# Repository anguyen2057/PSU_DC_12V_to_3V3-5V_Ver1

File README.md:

# PSU_DC_12V_to_3V3-5V_Ver1
Initial design compact switching power supply unit (PSU) that converts a 12V input to regulated 3.3V and 5V outputs.

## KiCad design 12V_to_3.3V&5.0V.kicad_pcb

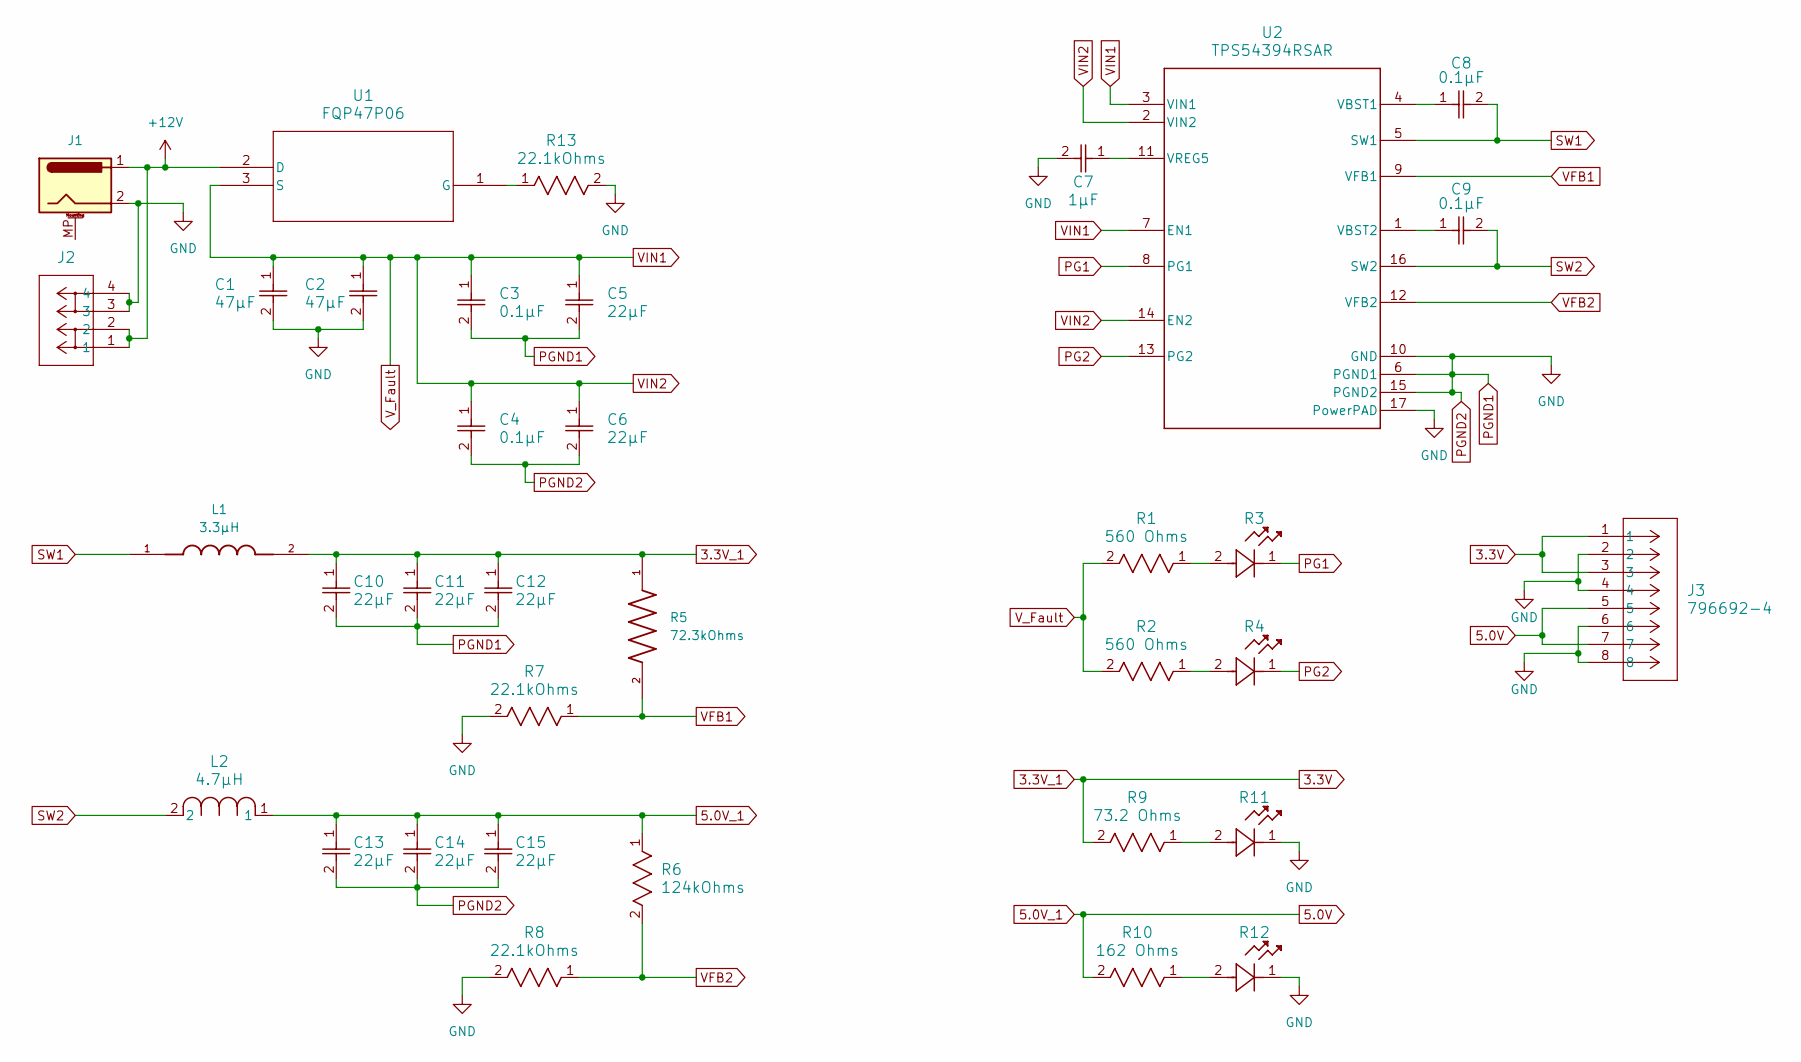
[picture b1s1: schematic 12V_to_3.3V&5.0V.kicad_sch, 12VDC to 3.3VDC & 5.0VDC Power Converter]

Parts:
C1, C2: 47µF; CAP_3216_TDK-M
C3, C4, C8, C9: 0.1µF; CAP_1005_TDK-M
C5, C6, C10, C11, C12, C13, C14, C15: 22µF; CAP_3216_TDK-M
C7: 1µF; CAP_2012_TDK-M
J1: Barrel_Jack_MountingPin; BarrelJack_Wuerth_6941xx301002
J2: 1017503; CONN_1017491
J3: 796692-4; CONN8_796692-4_TEC
L1: 3.3µH; IND_VLS6045EX-3R3N; PARTREV N/A; DigiKey_Part_Number 445-173052-2-ND
L2: 4.7µH; IND_VLS6045EX-4R7M_TDK-M
R1, R2: 560 Ohms; RC1206N_YAG-M
R3, R4, R11, R12: SML-E12DWT86; LED_SMLD12_ROM
R5: 72.3kOhms; RESC1608X55N; DigiKey_Part_Number 2019-RN73H1JTTD7232B25TR-ND
R6: 124kOhms; RES_TNPW1206_VIS-M
R7, R8, R13: 22.1kOhms; RES_TNPW1206_VIS-M
R9: 73.2 Ohms; RC1206N_YAG-M
R10: 162 Ohms; RC1206N_YAG-M
U1: FQP47P06; TO220-3_ONS
U2: TPS54394RSAR; RSA0016B-IPC_A

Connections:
3.3V: C10.1, C11.1, C12.1, J3.1, J3.3, L1.2, R5.1, R9.2
5.0V: C13.1, C14.1, C15.1, J3.5, J3.7, L2.1, R6.1, R10.2
+12V: J1.1, J2.1, J2.2, U1.2 (D)
unnamed: R1.1, R3.2
unnamed: R2.1, R4.2
unnamed: R10.1, R12.2
unnamed: R9.1, R11.2
unnamed: R13.1, U1.1 (G)
unnamed: C8.1, U2.4 (VBST1)
unnamed: C9.1, U2.1 (VBST2)
unnamed: C7.1, U2.11 (VREG5)
PG1: R3.1, U2.8 (PG1)
PG2: R4.1, U2.13 (PG2)
PGND1: C1.2, C2.2, C3.2, C4.2, C5.2, C6.2, C7.2, C10.2, C11.2, C12.2, C13.2, C14.2, C15.2, J1.2, J2.3, J2.4, J3.2, J3.4, J3.6, J3.8, R7.2, R8.2, R11.1, R12.1, R13.2, U2.6 (PGND1), U2.10 (GND), U2.15 (PGND2), U2.17 (PowerPAD)
SW1: C8.2, L1.1, U2.5 (SW1)
SW2: C9.2, L2.2, U2.16 (SW2)
VFB1: R5.2, R7.1, U2.9 (VFB1)
VFB2: R6.2, R8.1, U2.12 (VFB2)
VIN1: C1.1, C2.1, C3.1, C4.1, C5.1, C6.1, R1.2, R2.2, U1.3 (S), U2.2 (VIN2), U2.3 (VIN1), U2.7 (EN1), U2.14 (EN2)

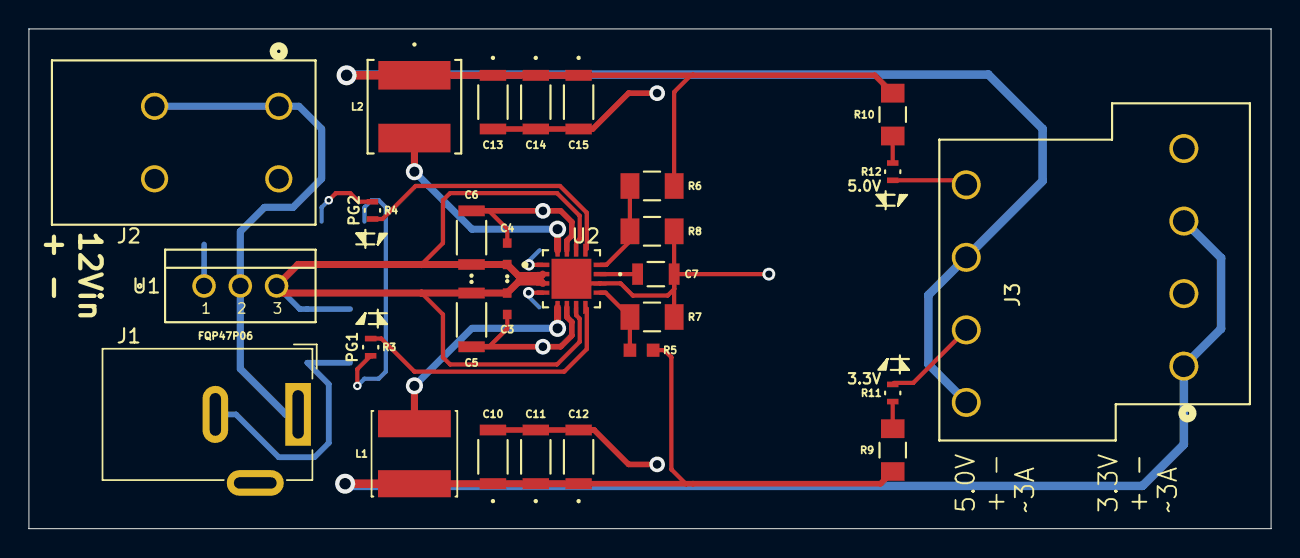
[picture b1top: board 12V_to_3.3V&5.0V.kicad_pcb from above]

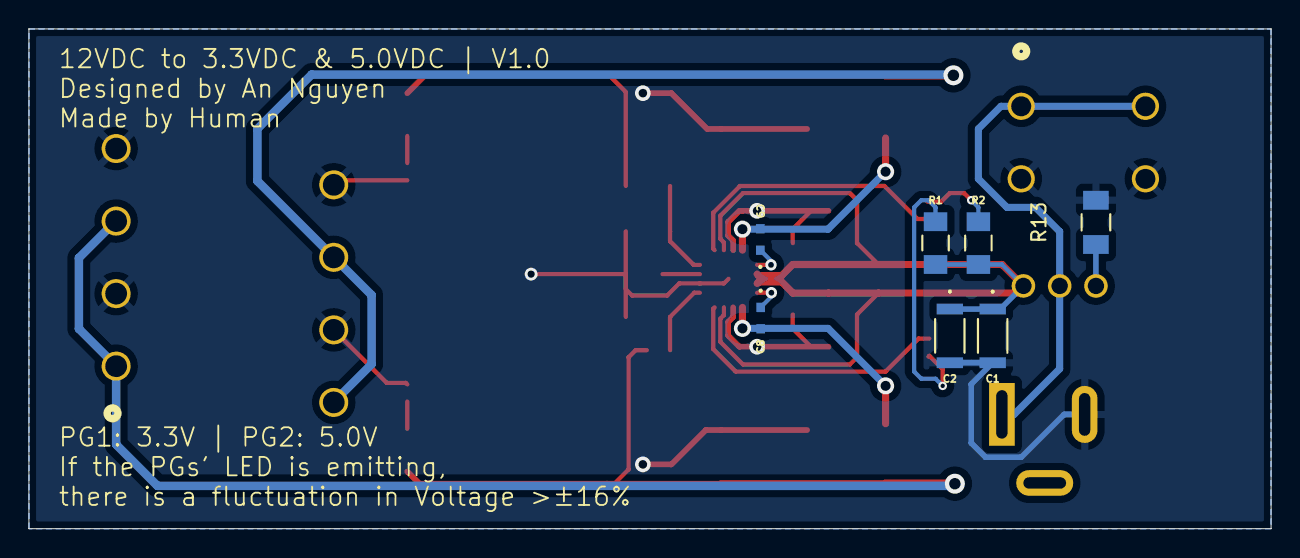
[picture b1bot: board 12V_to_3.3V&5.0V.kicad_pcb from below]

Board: 2 copper layers, 87.0 x 35.0 mm, 35 parts (7 on the bottom side), 19 nets.

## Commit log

2025-02-19 Initial commit - Adding the files to repo
